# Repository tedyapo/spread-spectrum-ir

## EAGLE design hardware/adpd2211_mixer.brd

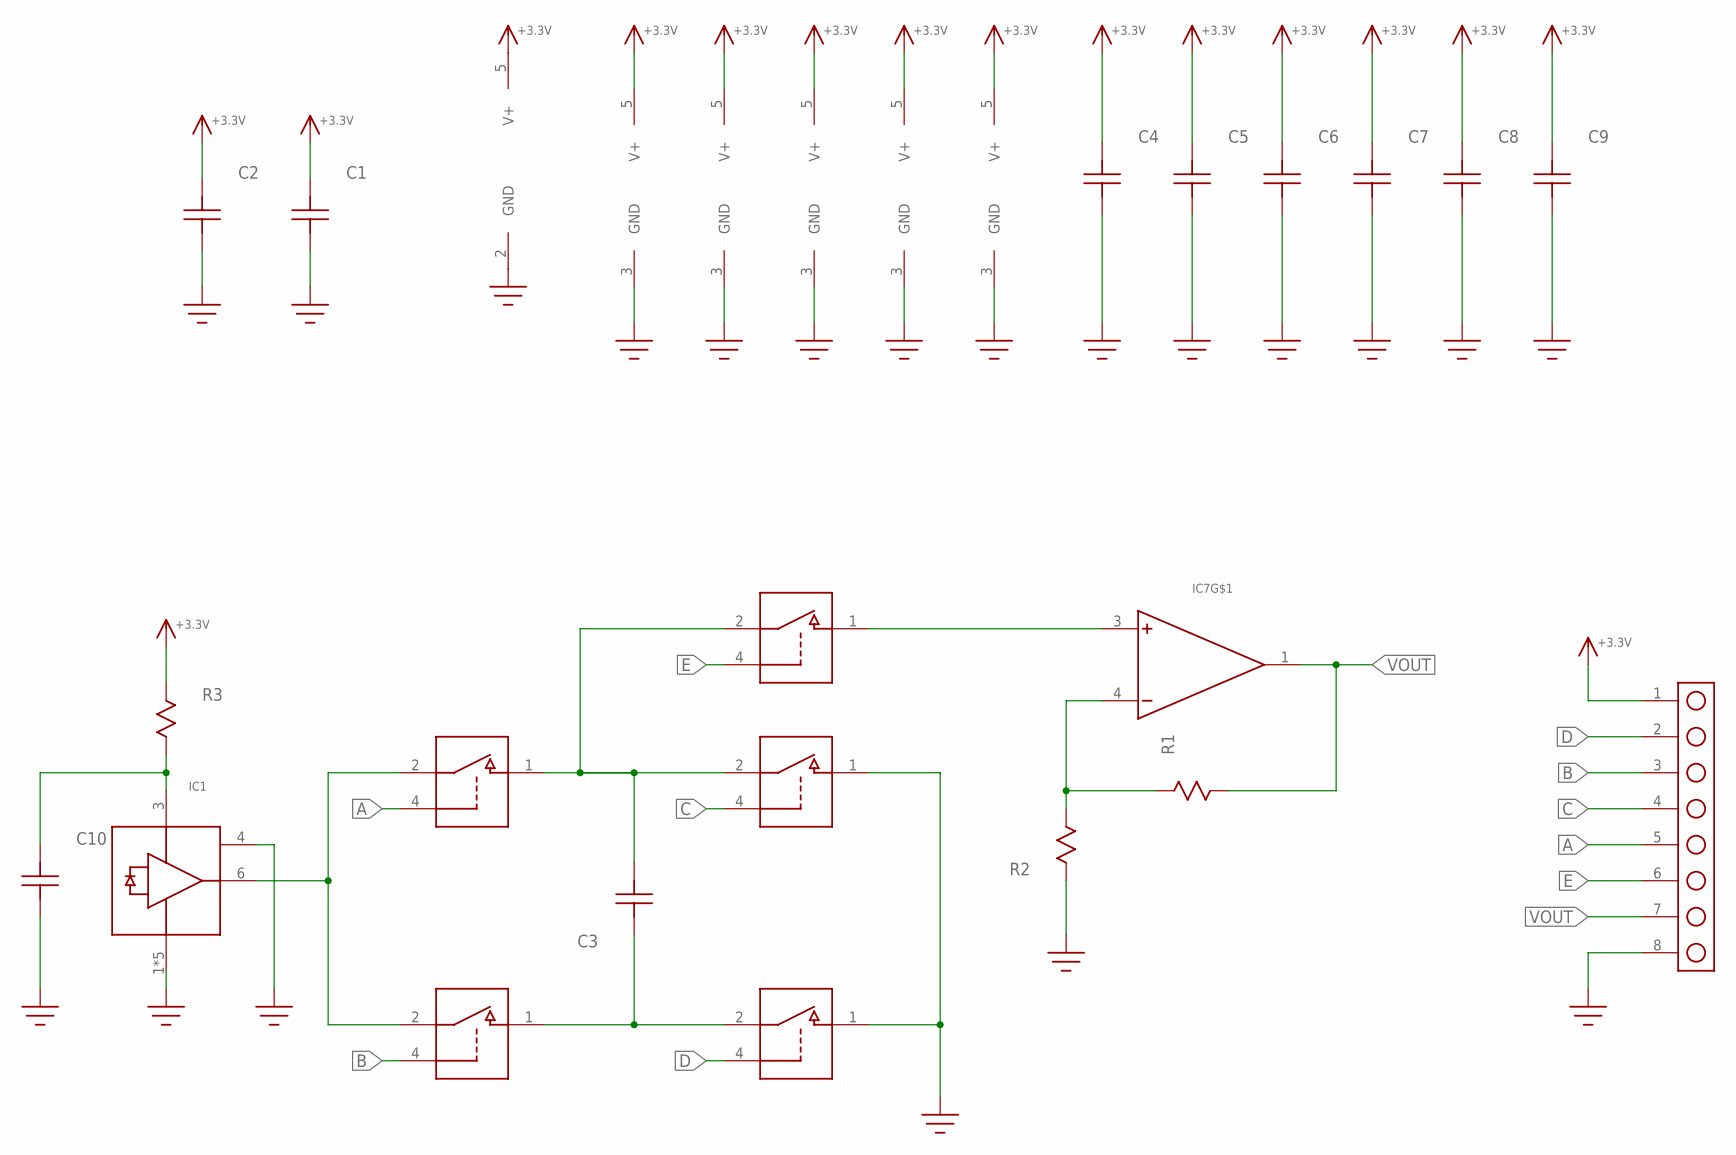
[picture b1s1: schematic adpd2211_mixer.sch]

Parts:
C1: C1206; 1206
C2, C4, C5, C6, C7, C8, C9, C10: C0603
C3: C0805; 0805
IC1: ADPD2211; LFCSP8
IC2, IC3, IC4, IC5, IC6: TS5A3166; SOT23-5
IC7: AD8538; SOT23-5
J1: HEADER_8_PIN
R1, R2, R3: R0603

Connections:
+3.3V: C1.P$2, C2.P$2, C4.P$2, C5.P$2, C6.P$2, C7.P$2, C8.P$2, C9.P$2, IC2.5 (V+), IC3.5 (V+), IC4.5 (V+), IC5.5 (V+), IC6.5 (V+), IC7.5 (V+), J1.1, R3.P$1
A: IC2.4 (IN), J1.5
B: IC4.4 (IN), J1.3
C: IC3.4 (IN), J1.4
D: IC5.4 (IN), J1.2
E: IC6.4 (IN), J1.6
GND: C1.P$1, C2.P$1, C4.P$1, C5.P$1, C6.P$1, C7.P$1, C8.P$1, C9.P$1, C10.P$1, IC1.1 (GND), IC1.2 (GND), IC1.4 (PWDN), IC1.5 (GND), IC1.7 (GND), IC1.8 (GND), IC2.3 (GND), IC3.1 (NO), IC3.3 (GND), IC4.3 (GND), IC5.1 (NO), IC5.3 (GND), IC6.3 (GND), IC7.2 (GND), J1.8, R2.P$1
unnamed: IC1.6 (OUT), IC2.2 (COM), IC4.2 (COM)
unnamed: C3.P$1, IC2.1 (NO), IC3.2 (COM), IC6.2 (COM)
unnamed: C3.P$2, IC4.1 (NO), IC5.2 (COM)
unnamed: C10.P$2, IC1.3 (VCC), R3.P$2
unnamed: IC6.1 (NO), IC7.3 (+)
unnamed: IC7.4 (-), R1.P$1, R2.P$2
VOUT: IC7.1 (OUT), J1.7, R1.P$2

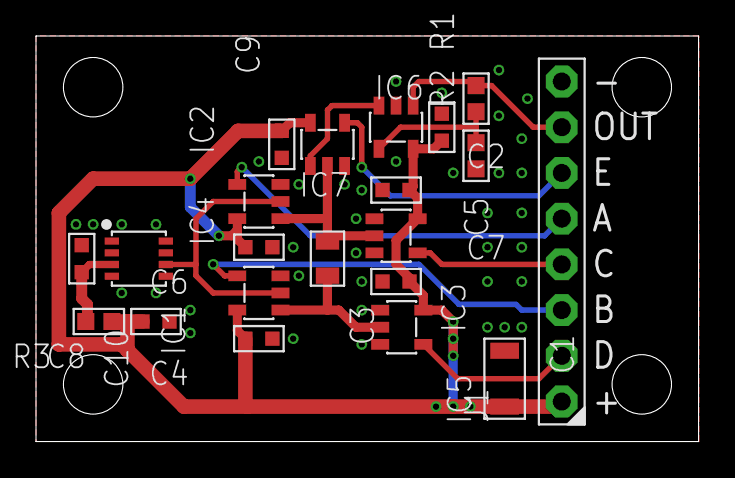
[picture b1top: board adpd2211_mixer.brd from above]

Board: 2 copper layers, 36.8 x 22.5 mm, 21 parts (0 on the bottom side), 14 nets.

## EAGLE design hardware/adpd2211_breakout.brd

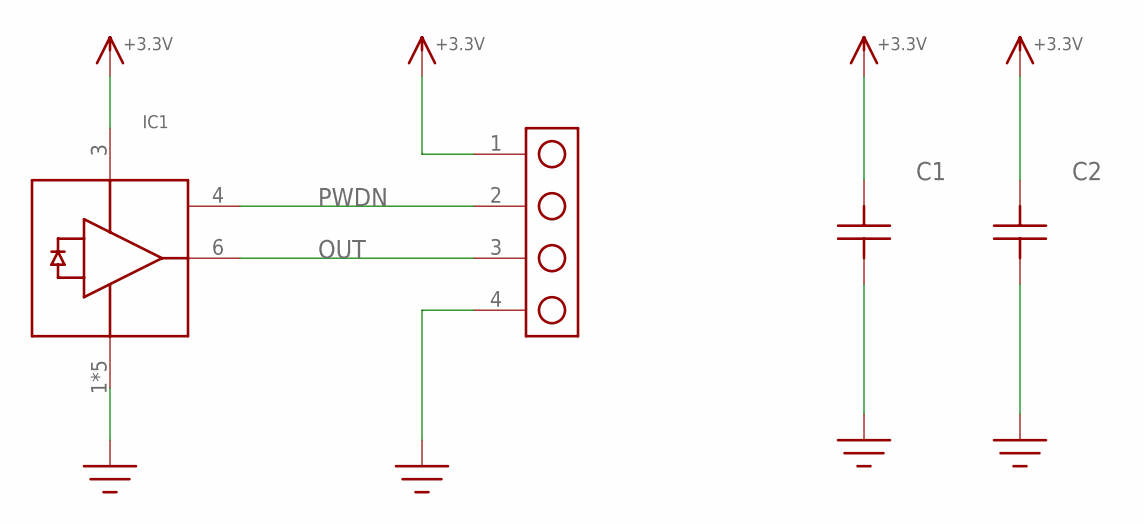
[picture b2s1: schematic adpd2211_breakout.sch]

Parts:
C1, C2: C0805; 0805
IC1: ADPD2211; LFCSP8
J1: HEADER_4_PIN; HEADER_4PIN

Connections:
+3.3V: C1.P$2, C2.P$2, IC1.3 (VCC), J1.1
GND: C1.P$1, C2.P$1, IC1.1 (GND), IC1.2 (GND), IC1.5 (GND), IC1.7 (GND), IC1.8 (GND), J1.4
OUT: IC1.6 (OUT), J1.3
PWDN: IC1.4 (PWDN), J1.2

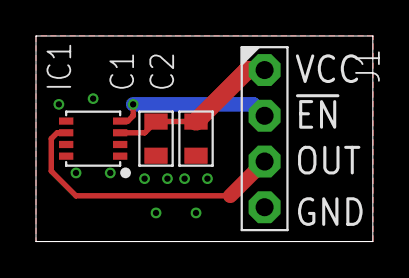
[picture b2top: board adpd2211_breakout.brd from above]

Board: 2 copper layers, 18.7 x 11.4 mm, 4 parts (0 on the bottom side), 4 nets.

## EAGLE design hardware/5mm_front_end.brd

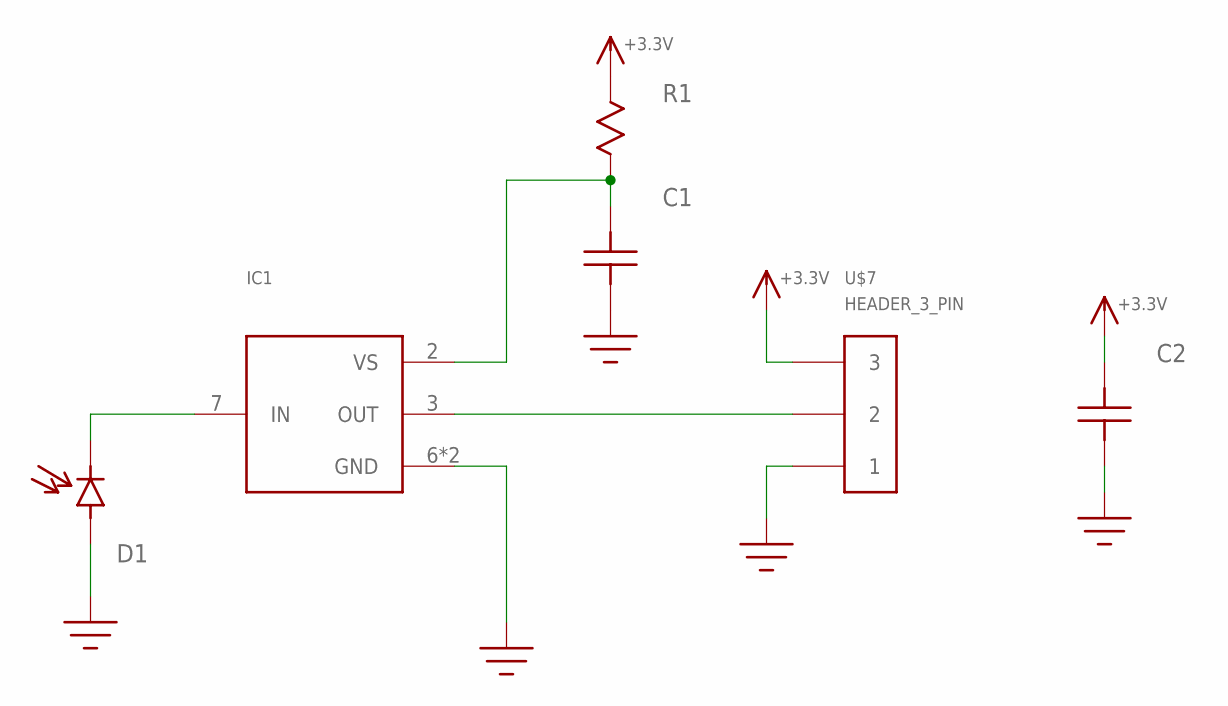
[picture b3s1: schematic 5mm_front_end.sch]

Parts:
C1: C0603
C2: C0805; 0805
D1: PHOTODIODE; LED_RA_5MM
IC1: VSOP98260
R1: R0603
U$7: HEADER_3_PIN

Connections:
+3.3V: C2.P$2, R1.P$1, U$7.3
GND: C1.P$1, C2.P$1, D1.A, IC1.6 (GND), IC1.8 (GND), U$7.1
unnamed: C1.P$2, IC1.2 (VS), R1.P$2
unnamed: D1.C, IC1.7 (IN)
unnamed: IC1.3 (OUT), U$7.2

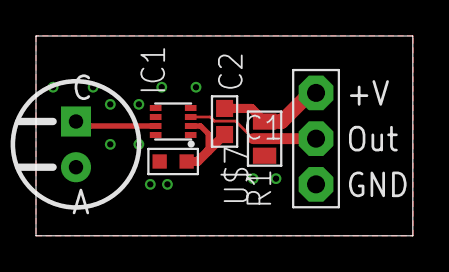
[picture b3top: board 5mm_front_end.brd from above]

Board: 2 copper layers, 20.9 x 11.1 mm, 6 parts (0 on the bottom side), 5 nets.

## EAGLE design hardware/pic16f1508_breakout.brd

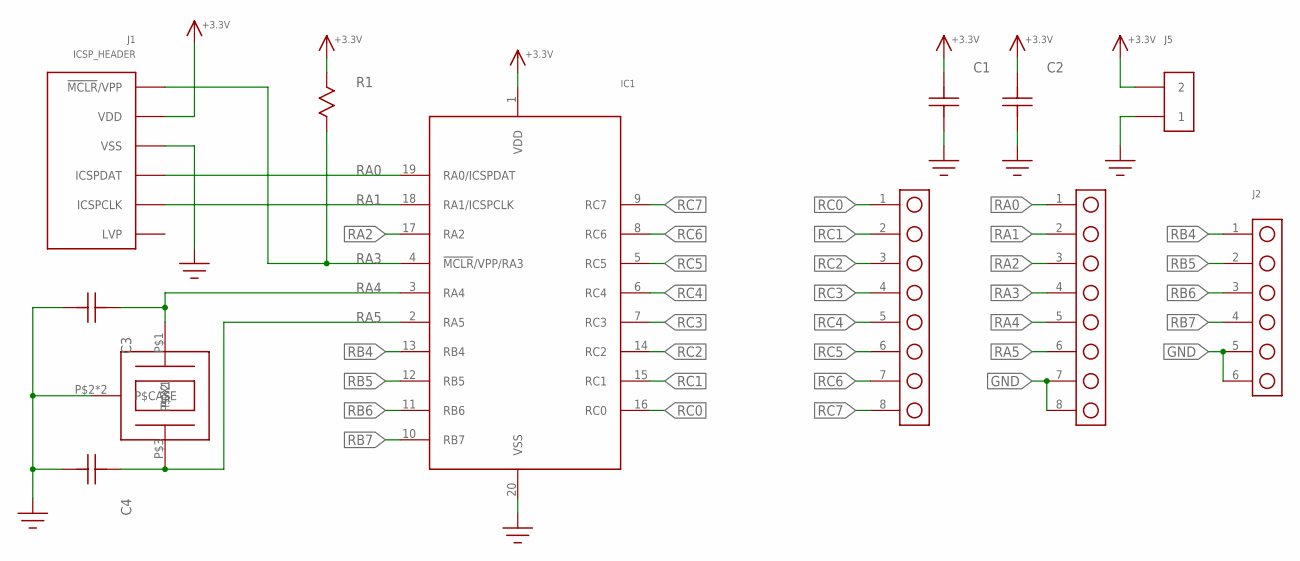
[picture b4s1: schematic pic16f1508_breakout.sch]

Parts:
C1: C1206; 1206
C2: C0805; 0805
C3, C4: C0603
IC1: PIC16F1508; 20SOIC_75
J1: ICSP_HEADER; HEADER_6P
J2: HEADER_6_PIN; HEADER_6P
J3, J4: HEADER_8_PIN
J5: HEADER_2_PIN
R1: R0805
U$10: XTAL; CRYSTAL_3.2X2.5

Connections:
+3.3V: C1.P$2, C2.P$2, IC1.1 (VDD), J1.2 (VDD), J5.2, R1.P$1
GND: C1.P$1, C2.P$1, C3.P$1, C4.P$1, IC1.20 (VSS), J1.3 (VSS), J2.5, J2.6, J4.7, J4.8, J5.1, U$10.P$2 (P$CASE), U$10.P$4 (P$CASE)
RA0: IC1.19 (RA0/ICSPDAT), J1.4 (ICSPDAT), J4.1
RA1: IC1.18 (RA1/ICSPCLK), J1.5 (ICSPCLK), J4.2
RA2: IC1.17 (RA2), J4.3
RA3: IC1.4 (!MCLR!/VPP/RA3), J1.1 (!MCLR!/VPP), J4.4, R1.P$2
RA4: C3.P$2, IC1.3 (RA4), J4.5, U$10.P$1 (P$X1)
RA5: C4.P$2, IC1.2 (RA5), J4.6, U$10.P$3 (P$X2)
RB4: IC1.13 (RB4), J2.1
RB5: IC1.12 (RB5), J2.2
RB6: IC1.11 (RB6), J2.3
RB7: IC1.10 (RB7), J2.4
RC0: IC1.16 (RC0), J3.1
RC1: IC1.15 (RC1), J3.2
RC2: IC1.14 (RC2), J3.3
RC3: IC1.7 (RC3), J3.4
RC4: IC1.6 (RC4), J3.5
RC5: IC1.5 (RC5), J3.6
RC6: IC1.8 (RC6), J3.7
RC7: IC1.9 (RC7), J3.8

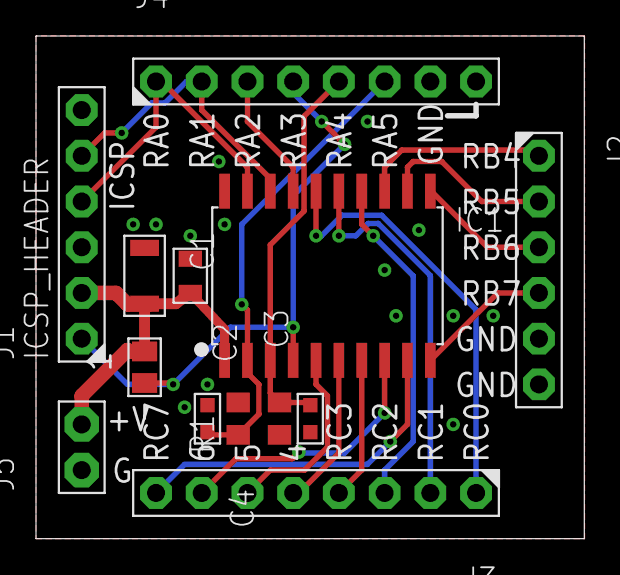
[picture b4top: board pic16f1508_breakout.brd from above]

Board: 2 copper layers, 30.5 x 27.9 mm, 12 parts (0 on the bottom side), 20 nets.

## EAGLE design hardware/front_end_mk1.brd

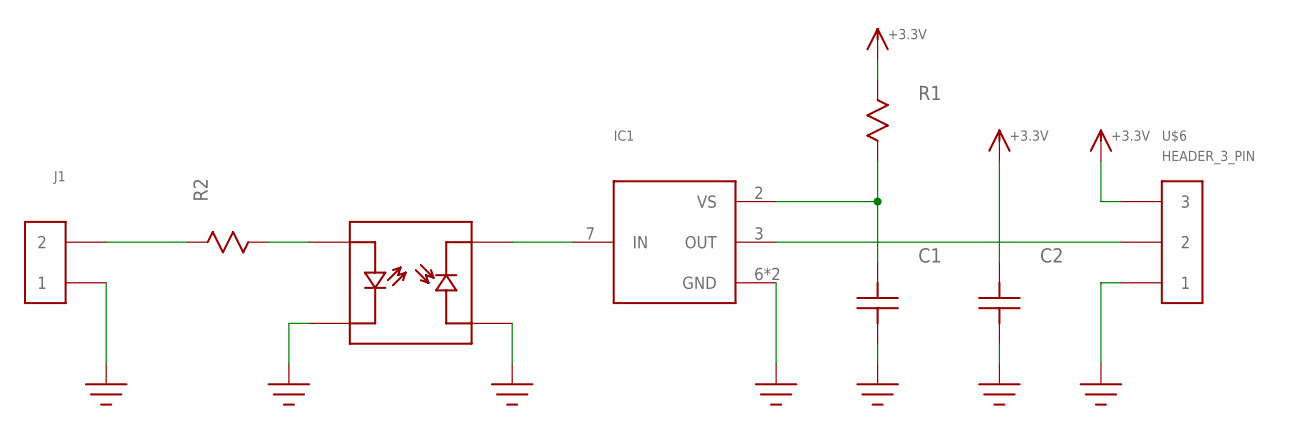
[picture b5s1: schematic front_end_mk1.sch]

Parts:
C1: C0603
C2: C0805; 0805
IC1: VSOP98260
IC2: HSDL-9100; HDSL-9100
J1: HEADER_2_PIN
R1: R0603
R2: R1206
U$6: HEADER_3_PIN

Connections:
+3.3V: C2.P$2, R1.P$1, U$6.3
GND: C1.P$1, C2.P$1, IC1.6 (GND), IC1.8 (GND), IC2.2 (LED_CATHODE), IC2.3 (PHOTODIODE_ANODE), J1.1, U$6.1
unnamed: IC1.7 (IN), IC2.4 (PHOTODIODE_CATHODE)
unnamed: C1.P$2, IC1.2 (VS), R1.P$2
unnamed: IC2.1 (LED_ANODE), R2.P$2
unnamed: IC1.3 (OUT), U$6.2
unnamed: J1.2, R2.P$1

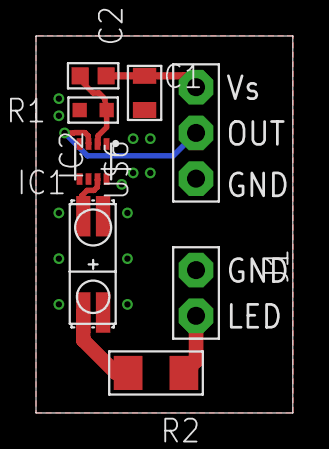
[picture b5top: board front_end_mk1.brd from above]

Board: 2 copper layers, 14.3 x 20.9 mm, 8 parts (0 on the bottom side), 7 nets.

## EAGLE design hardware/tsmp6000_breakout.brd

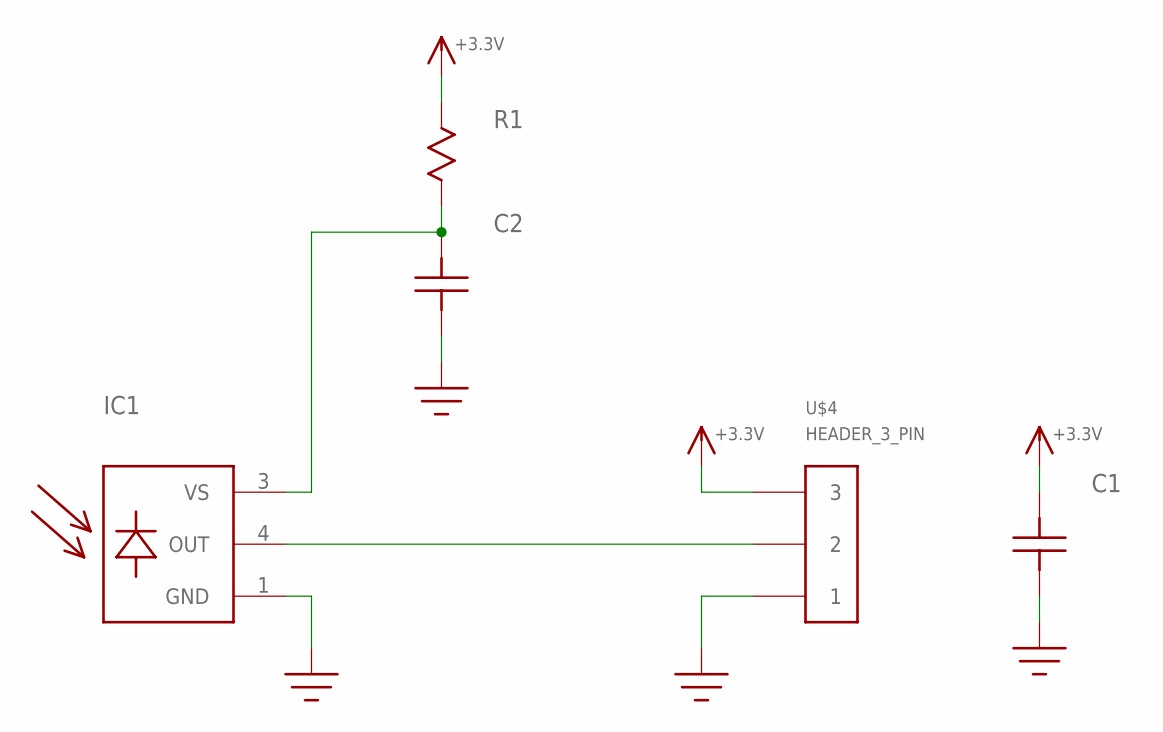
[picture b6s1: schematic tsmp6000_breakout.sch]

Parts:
C1: C1206; 1206
C2: C0805; 0805
IC1: TSMP6000
R1: R0805
U$4: HEADER_3_PIN

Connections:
+3.3V: C1.P$2, R1.P$1, U$4.3
GND: C1.P$1, C2.P$1, IC1.1 (GND), U$4.1
unnamed: C2.P$2, IC1.3 (VS), R1.P$2
unnamed: IC1.4 (OUT), U$4.2

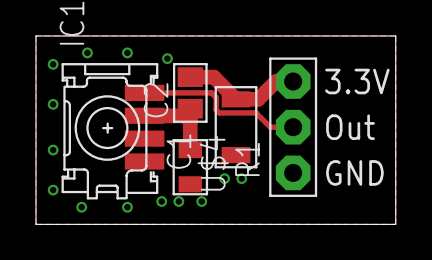
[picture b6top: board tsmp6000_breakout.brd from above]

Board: 2 copper layers, 20.0 x 10.5 mm, 5 parts (0 on the bottom side), 4 nets.

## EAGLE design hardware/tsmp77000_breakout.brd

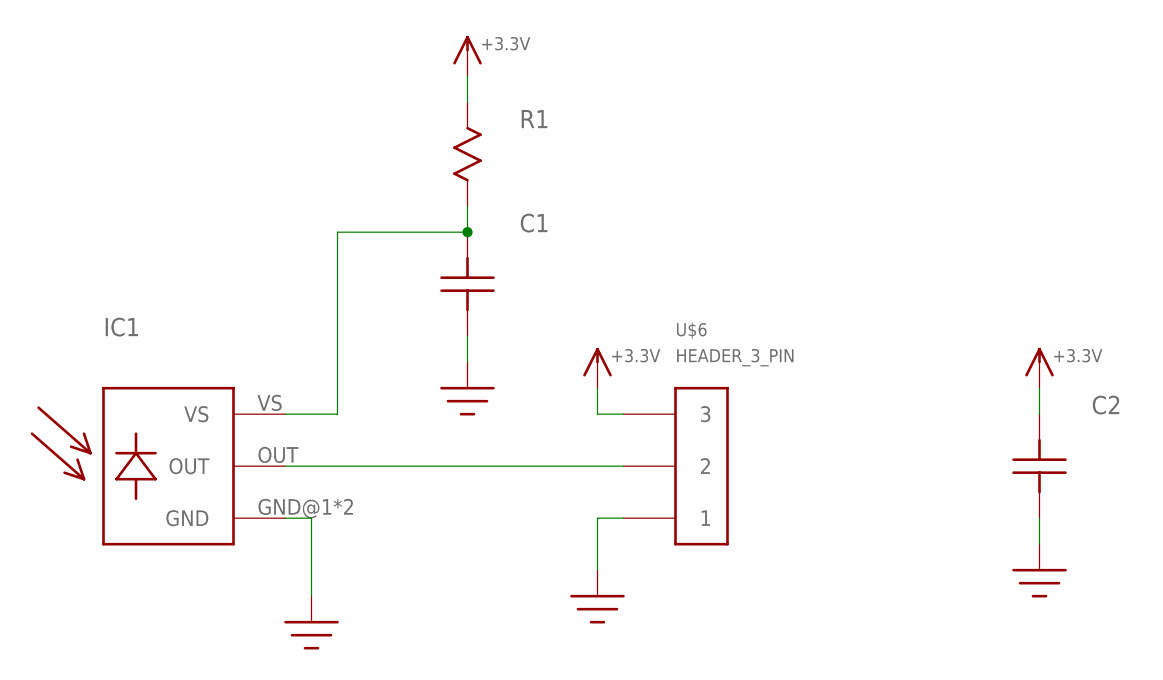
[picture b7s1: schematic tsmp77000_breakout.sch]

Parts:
C1: C0805; 0805
C2: C1206; 1206
IC1: TSMP77000
R1: R0805
U$6: HEADER_3_PIN

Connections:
+3.3V: C2.P$2, R1.P$1, U$6.3
GND: C1.P$1, C2.P$1, IC1.GND@1 (GND), IC1.GND@2 (GND), U$6.1
unnamed: C1.P$2, IC1.VS, R1.P$2
unnamed: IC1.OUT, U$6.2

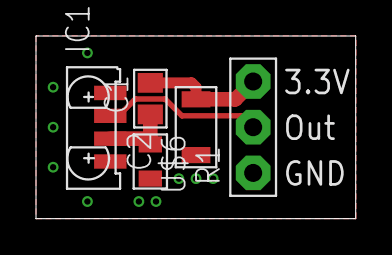
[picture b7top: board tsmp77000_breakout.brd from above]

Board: 2 copper layers, 17.8 x 10.1 mm, 5 parts (0 on the bottom side), 4 nets.

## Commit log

2018-03-14 first files
2018-03-20 breakouts and test PCBs
2018-03-28 created breakout for ADPD2211 and mixer PCB
